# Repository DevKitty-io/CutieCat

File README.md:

# CutieCat
Build your own Cat-Themed console for hacking & hardware prototyping, based around the [Adafruit QT-PY]() microcontroller!
*Learn more at [DevKitty.io](https://devkitty.io)*.

<!--  -->

#### Quick Resources:
- [Assembly Guide](https://hackster.io)
- [Usage Docs](https://docs.devkitty.io/cutiecat)
- [Design Choices](#design-choices)

## Version
### Change Log

##### PCB: `v1.1`  
- Increased header margin
- Swapped soft buttons for clicky buttons (better feel)
- THT compatible Xiao / QT-Py footprint
- Annotate step #2 + tape area 

##### Case: `r1.1`
- `r1.0` Same enclosure as `v1.0` PCB
- `r1.0` New D-Pad (increase height)
- `r1.1` Universal top design - just swap the backplate! (see pic)
- `r1.2` TODO - hex cutouts, multiple SMA backplates
- `r1.3` TODO - threaded & rugged cases

### Naming convention:
`ver_name_mod_rev` eg: (`v1.1_CutieCat-Case_Top-S1_r1.1`)  

`ver` denotes the main PCB revision, which enclosure designs + mods revolve around.  To disambiguify changes to enclosures etc. a `rev` number is used.

`S#` in case files indicate how many SMA ports are accomodated.   
   
## Contents
- **src**
   - **pcb**: KiCAD PCB design files **
   - **cases**: FreeCAD enclosure design files
- **exports**: ready to print enclosures
- **assets**: board outline, graphic art for design, renders

***If you wish to order PCB's, you'll have to export them yourself*

## Circuit Board
CutieCat is designed to be accessible & affordable for beginners - whether you want to get started soldering or hacking!  The design uses off-the-shelf components available on Amazon, and you can even [fabricate the PCB](https://pcbway.com) yourself. 

### Main Components
|Name|Details|Number|
|---|---|---|
|Screen|SH1106 1.3" I2C OLED|1|
|Microcontroller|QT Py / Seeed Xiao|1|
|Expansion Header|6-Pin Female 2.54mm|1|

### Other Components
|Name|Details|Number|
|---|---|---|
|Buttons|`5.3 x 5.3 x 1.5` Tactile Buttons|4|
|RGB LED|SK6812 "NeoPixel"|1|
|SD Card|Push-Push Style|1|
|Qwiic-Style Exansion|JST SH SM04B|2|

### Design Choices
*pictures coming*

##### Microcontroller
The [Seeed Xiao](), also compatible with the [Adafruit QT-Py](), is a low-profile microcontroller form factor.  You can solder it directly on the board with the castellated pads - or use through-hole headers if you're not comfortable with SMD!

Both brands offer breakouts for popular MCU's like the RP2040, SAMD, and my favorite - the ESP32.  CutieCat ships with an ESP32 since our firmware is built to teach educational hacking.

But you can easily swap in your own microcontroller!  There's even plenty of modular, compatible add-on boards from [Seeed]() or [Adafruit]().

##### Screen
The `SH1106` is a ubiquitous screen in the common `128x64` resolution.  These cheap screens sometimes have swapped pins so I added a square matrix that lets you switch them with and exacto blade and solder.

Pads on the board topside are slightly larger in case I ever design a castellated version of the SH1106 that mounts flush.  

Sticky tape is used instead to standoff the off-the-shelf SH1106.

##### Expansion
You can expand using the onboard header or **modchip** area.  Both breakout UART and I2C with 3.3v - as most peripherals are - but USB / 5V power is available through probe pads if needed.

**Minimeter** is a propietary charging circuit I made after getting pissed off with the unavailability of drop-in charging solutions.  You can also read the battery level over I2C.  [Eventually you can buy one here.](shop.devkitty.io/minimeter)

##### Antenna
Whether you want to solder on a second microcontroller for Bluetooth Recon or GPS for wardriving - you can benefit from external antennas!  

The "ears" originally fit an `M2.5` threaded screw but I decided later down the line to widen them slightly to accomodate these [u.fl to SMA]() board-mount antennas.

##### Peripherals
**Buttons**: I was very fond of the soft buttons used in `v1.0` - but they felt too gummy behind a 3D printed D-Pad so low-profile clicky ones were selected instead.

**Connectors**: UART & I2C are broken out in [Qwiic]() style headers - which support hundreds of [Adafruit]() and [Sparkfun]() sensors.  

**SD Card**: It uses SPI - a communication protocol that typically requires a select pin to switch between other devices also using SPI.  Since there weren't enough pins, I tied `CS` (chip select to ground).  You can cut the CS trace if you wish to use other SPI peripherals.

**NeoPixel**: I had space so why not?  Uses the SK6812 RGB LED, on the MCU RX pin.  

## Enclosure
The case should be as modular as possible to reduce waste.  I designed a single "top" enclosure with 2 circular SMA cutouts if the user chooses to solder those on later.

The bottom enclosures can be printed with necessary SMA cutouts.

##### Versions
- `S0/S1/S2`: Denotes number of SMA cutouts
- `Hex`: Hex pattern cutout
- `Rugged`: 1/4" 20 compatible threaded mounting

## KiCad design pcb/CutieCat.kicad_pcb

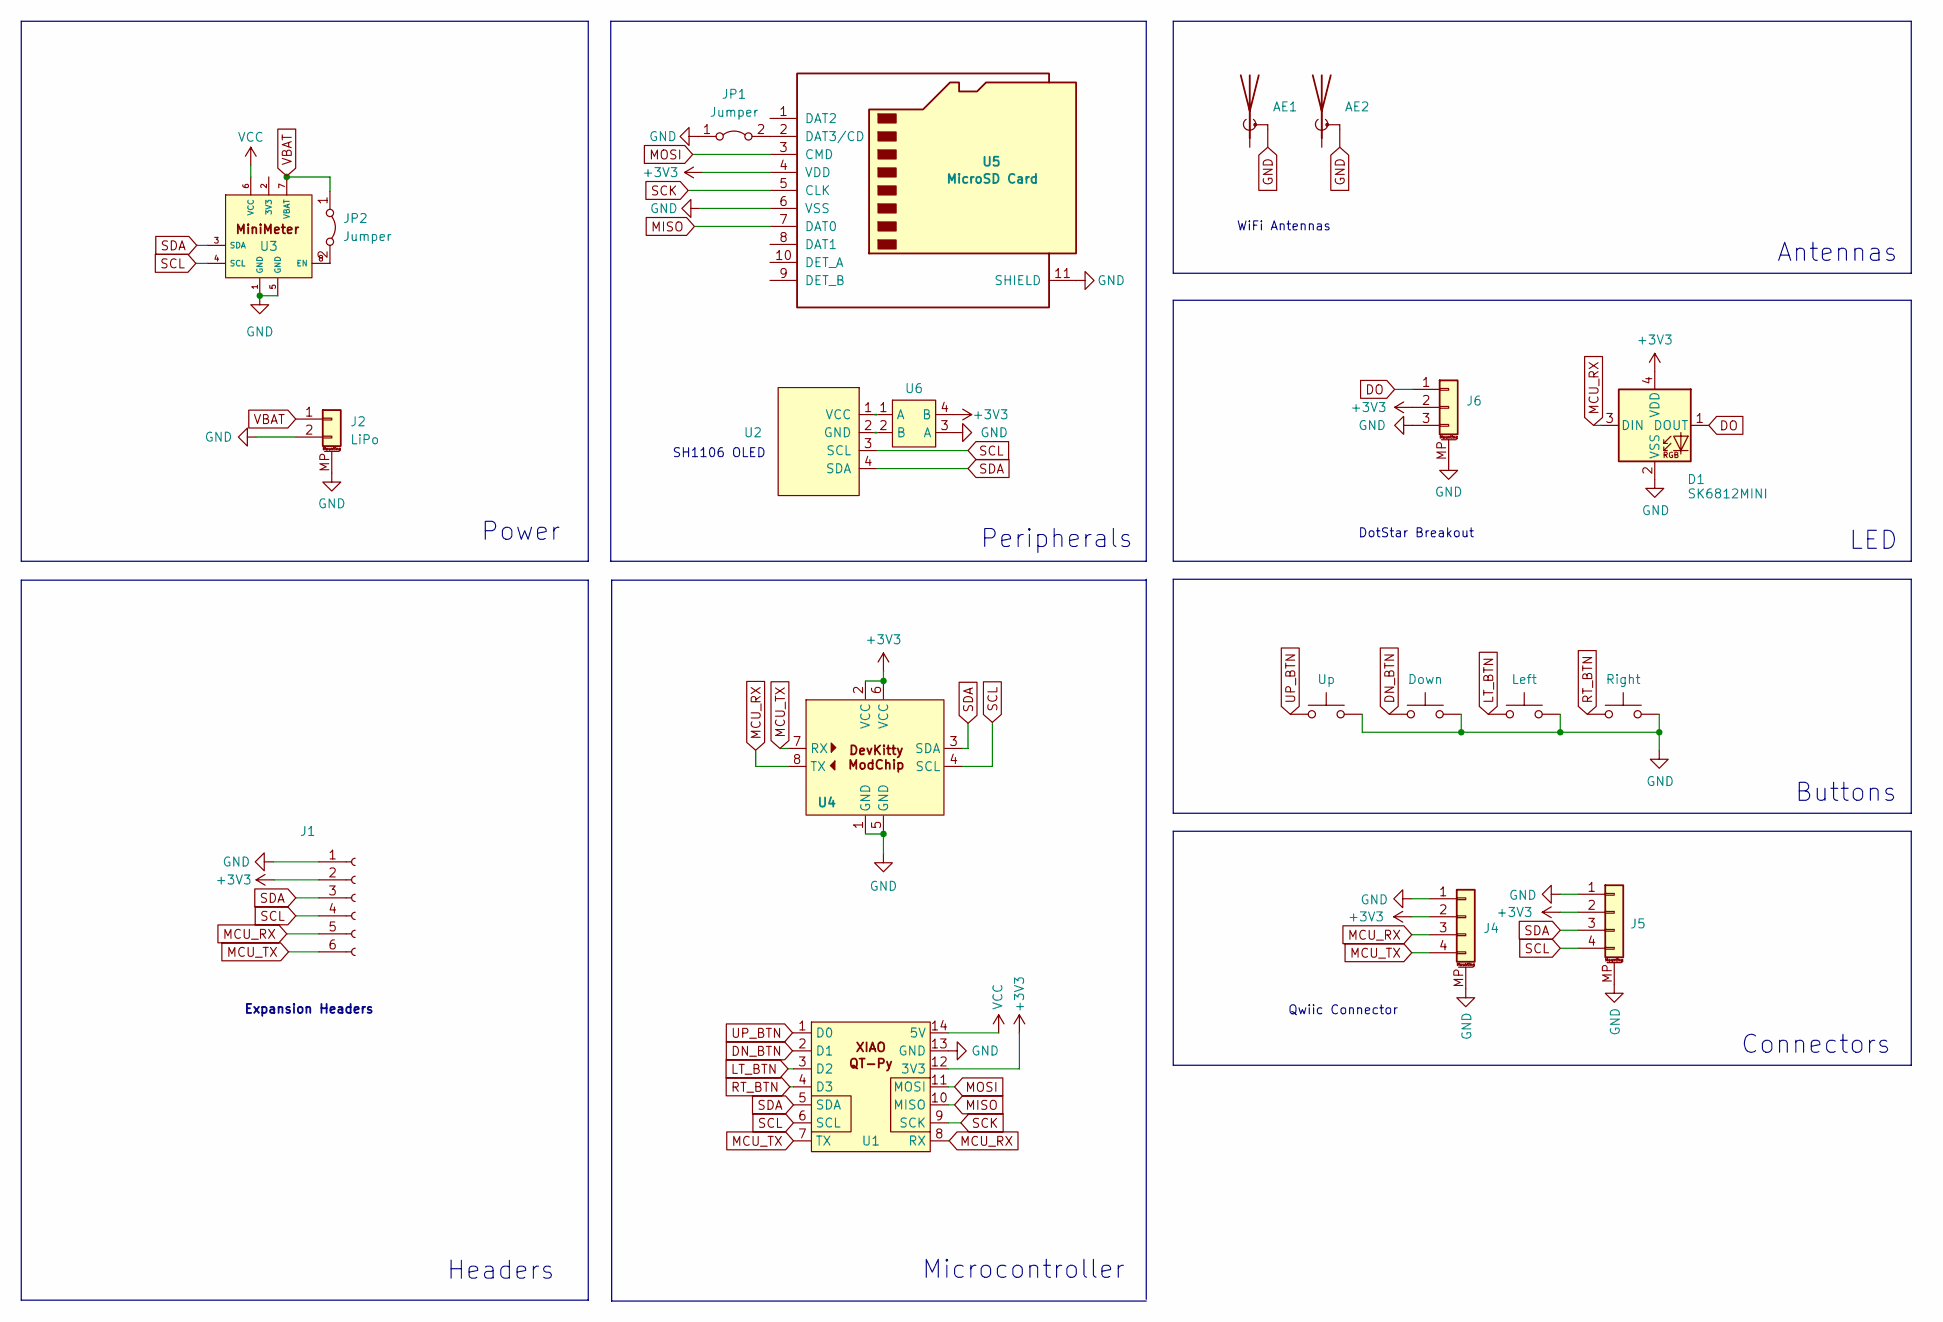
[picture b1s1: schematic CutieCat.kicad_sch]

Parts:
AE1, AE2: Antenna_Shield; SMA_Amphenol_901-144_Vertical
D1: SK6812MINI; LED_SK6812MINI_PLCC4_3.5x3.5mm_P1.75mm
J1: Header; SolderJumper-2_P1.3mm_Bridged_RoundedPad1.0x1.5mm
J2: LiPo
J4, J5: Conn_01x04_MountingPin
J6: Conn_01x03_MountingPin
JP1, JP2: Jumper; SolderJumper-2_P1.3mm_Bridged_RoundedPad1.0x1.5mm
SW1: Up; SW_SPST_FSMSM
SW2: Down; SW_SPST_FSMSM
SW3: Left; SW_SPST_FSMSM
SW4: Right; SW_SPST_FSMSM
U1: JST_PH_S2B-PH-SM4-TB_1x02-1MP_P2.00mm_Horizontal
U2: SH1106 OLED; SH1106
U3, U4, U6: (no value)
U5: MicroSD Card; MicroSD

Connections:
+3V3: D1.4 (VDD), J1.2, J4.2, J5.2, J6.2, U1.12 (3V3), U4.2 (VCC), U4.6 (VCC), U5.4 (VDD), U6.4 (B)
DN_BTN: SW2.1, U1.2 (D1)
DO: D1.1 (DOUT), J6.1
GND: AE1.1 (A), AE1.2 (Shield), AE2.1 (A), AE2.2 (Shield), D1.2 (VSS), J1.1, J2.2, J2.MP (MountPin), J4.1, J4.MP (MountPin), J5.1, J5.MP (MountPin), J6.3, J6.MP (MountPin), JP1.1 (A), SW1.2, SW2.2, SW3.2, SW4.2, U1.13 (GND), U3.1 (GND), U3.5 (GND), U4.1 (GND), U4.5 (GND), U5.6 (VSS), U5.11 (SHIELD), U6.3 (A)
LT_BTN: SW3.1, U1.3 (D2)
MCU_RX: D1.3 (DIN), J1.5, J4.3, U1.8 (RX), U4.8 (TX)
MCU_TX: J1.6, J4.4, U1.7 (TX), U4.7 (RX)
MISO: U1.10 (MISO), U5.7 (DAT0)
MOSI: U1.11 (MOSI), U5.3 (CMD)
unnamed: JP1.2 (B), U5.2 (DAT3/CD)
unnamed: JP2.2 (B), U3.8 (EN)
unnamed: U2.2 (GND), U6.2 (B)
unnamed: U2.1 (VCC), U6.1 (A)
RT_BTN: SW4.1, U1.4 (D3)
SCK: U1.9 (SCK), U5.5 (CLK)
SCL: J1.4, J5.4, U1.6 (SCL), U2.3 (SCL), U3.4 (SCL), U4.4 (SCL)
SDA: J1.3, J5.3, U1.5 (SDA), U2.4 (SDA), U3.3 (SDA), U4.3 (SDA)
UP_BTN: SW1.1, U1.1 (D0)
VBAT: J2.1, JP2.1 (A), U3.7 (VBAT)
VCC: U1.14 (5V), U3.6 (VCC)

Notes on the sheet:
Qwiic Connector
Connectors
Power
Buttons
WiFi Antennas
DotStar Breakout
Antennas
Expansion Headers
LED
Peripherals
SH1106 OLED
Headers
Microcontroller

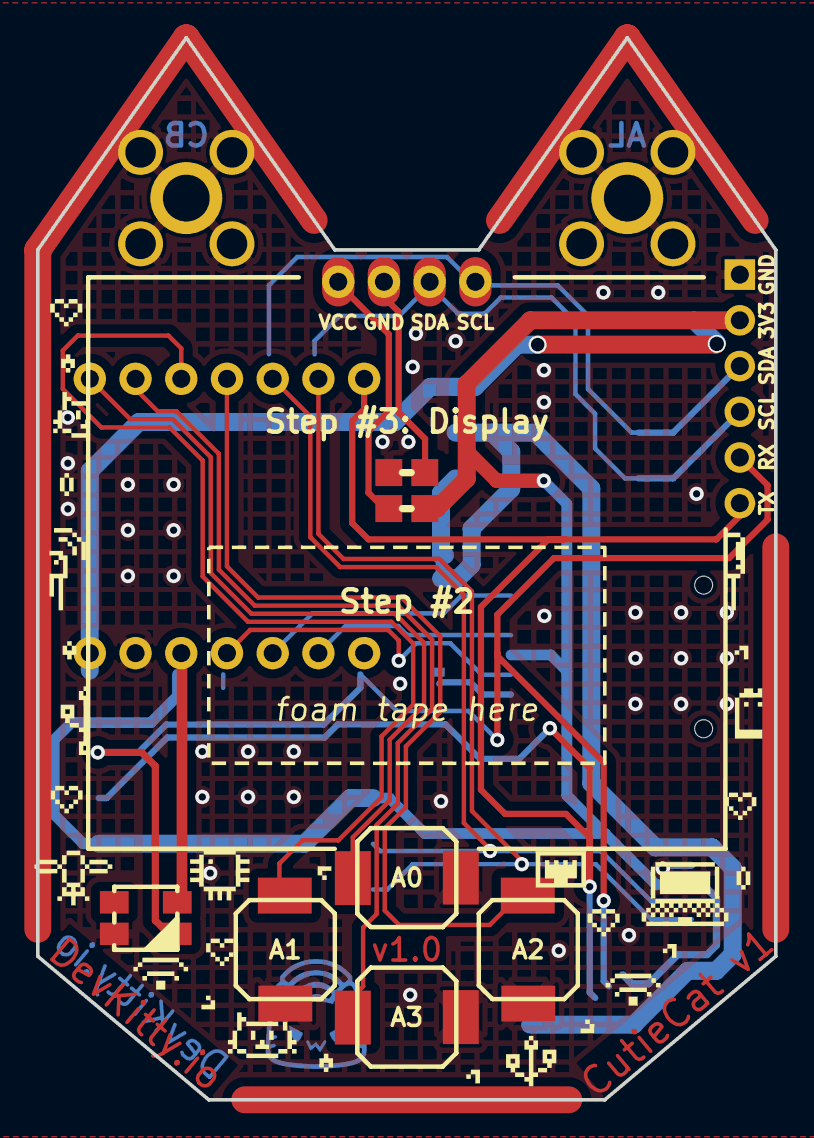
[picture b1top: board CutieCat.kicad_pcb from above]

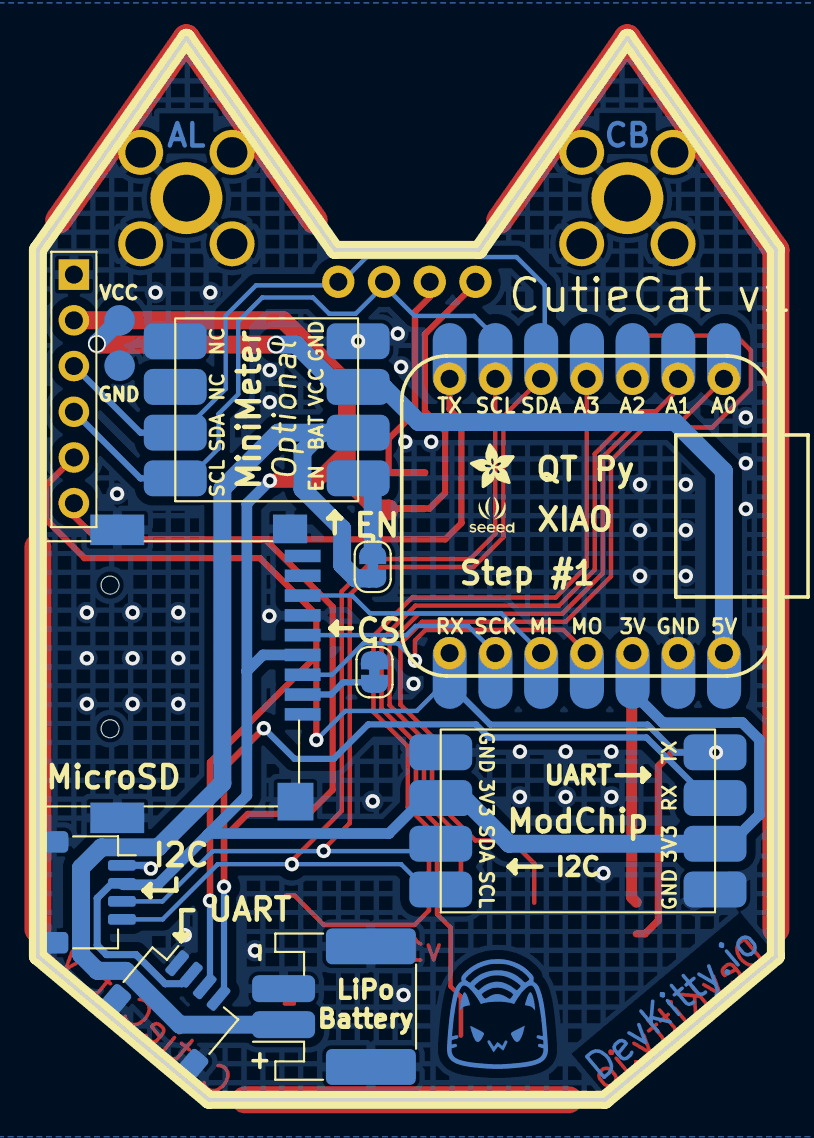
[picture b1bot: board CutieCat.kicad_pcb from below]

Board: 2 copper layers, 41.0 x 59.0 mm, 20 parts (13 on the bottom side), 19 nets.

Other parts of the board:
Gf: LOGO

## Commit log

2024-02-21 add v0.0 CutieCat source files + gerbers
2024-02-21 add render
2024-09-20 remove old case design
2024-09-21 update v0.1 case w/ slightly reduced standoff & reinforced snap joint
2024-11-21 push v0.1 pcb
2024-11-23 push v1.0 PCB & README
2024-11-23 move some files & update render
2024-11-23 ignore files
2024-12-19 add v1 and delete old files
2024-12-19 update pcb
2024-12-19 addadd pcb 3d model
2025-02-17 update PCB & case design
2025-02-19 update model
2025-03-08 add changelog + parts justification
2025-03-17 fix silkscreen I2C error
